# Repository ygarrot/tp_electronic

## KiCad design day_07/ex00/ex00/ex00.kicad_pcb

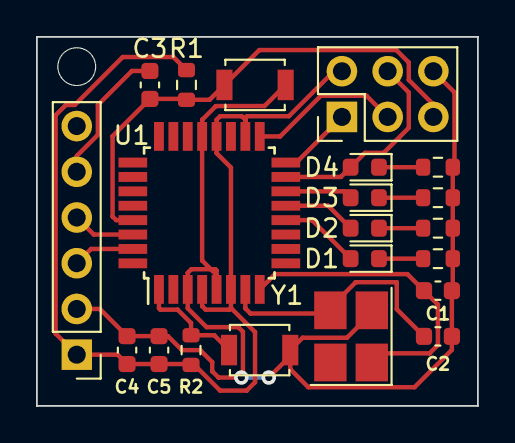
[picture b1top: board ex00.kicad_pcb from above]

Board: 2 copper layers, 24.5 x 20.5 mm, 22 parts (0 on the bottom side), 19 nets.

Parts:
C1, C2: 22pF; C_0603_1608Metric
C3, C4: 100nF; C_0603_1608Metric
C5: 10uF; C_0603_1608Metric
D1, D2, D3, D4: LED_Filled; LED_0603_1608Metric
H1: MountingHole; MountingHole_2.1mm
J1: Conn_01x06; PinHeader_1x06_P2.54mm_Vertical
J2: AVR-ISP; PinHeader_2x03_P2.54mm_Vertical
R1, R2: 10K; R_0603_1608Metric
R3, R4, R5, R6: 330R; R_0603_1608Metric
SW1, SW2: SW_Push; SW_SPST_B3U-1000P
U1: ATmega48PV-10A; TQFP-32_7x7mm_P0.8mm
Y1: 16MHz; Crystal_SMD_3225-4Pin_3.2x2.5mm_HandSoldering

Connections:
+5V: C4.1, C5.1, J1.1, J2.2 (VCC), R1.1, R2.1, U1.4 (VCC), U1.6 (VCC), U1.18 (AVCC), U1.20 (AREF)
/BUT_0: R2.2, SW2.1, U1.1 (PD3)
/LED_0: D1.2 (A), U1.12 (PB0)
/LED_1: D2.2 (A), U1.13 (PB1)
/LED_2: D3.2 (A), U1.14 (PB2)
/LED_3/MOSI: D4.2 (A), J2.4 (MOSI), U1.15 (PB3)
/MCU_RX: J1.4, U1.30 (PD0)
/MCU_TX: J1.3, U1.31 (PD1)
/MISO: J2.1 (MISO), U1.16 (PB4)
/SCK: J2.3 (SCK), U1.17 (PB5)
/XTAL1: C2.1, U1.7 (XTAL1/PB6), Y1.3
/XTAL2: C1.1, U1.8 (XTAL2/PB7), Y1.1
/~RESET: C3.2, J2.5 (~RST), R1.2, SW1.1, U1.29 (~RESET/PC6)
GND: C1.2, C2.2, C4.2, C5.2, J1.2, J2.6 (GND), R3.2, R4.2, R5.2, R6.2, SW1.2, SW2.2, U1.3 (GND), U1.5 (GND), U1.21 (GND), Y1.2
unnamed: C3.1, J1.5
unnamed: D1.1 (K), R3.1
unnamed: D2.1 (K), R4.1
unnamed: D3.1 (K), R5.1
unnamed: D4.1 (K), R6.1

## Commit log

2022-01-10 light a led
2022-01-10 delay refacto
2022-01-10 reworking on day/night
2022-01-10 still working on delayt
2022-01-11 used isr, but interrupt are not allowe
2022-01-11 its finally working wihtout loop
2022-01-11 day 00
2022-01-12 day 02
2022-01-12 ex 01 day 01
2022-01-12 clean the doc
2022-01-13 ex00 day 03
2022-01-13 ex02 day 03
2022-01-13 ex 04
2022-01-13 ex01 day 02
2022-01-13 done fixing typo in ex01
2022-01-13 ex06 day00
2022-01-14 use macro for delay because inline function doesn't work properly
2022-01-14 clear code, clear mind
2022-01-14 macro everywhere
2022-01-14 comment ex01 day 01
2022-01-14 comment day 2 3
2022-01-14 clean dupplicated code
2022-01-14 login done
2022-01-19 update day_00
2022-01-19 day 05
2022-01-20 restore day 04
2022-01-20 ex01 day 5
2022-01-20 remove unused files and folder
2022-01-20 adc done (ex00 day 06)
2022-01-21 ex02 - temperature
2022-01-21 remove opti flag
2022-01-21 ex 04 couleur analogique
2022-01-21 day06 done
2022-01-21 tech 1 ex 03 done // day done
2022-01-21 int1 instead of int0 because button change from pd3 to pd2
2022-01-21 day 04
2022-01-25 day_07
2022-01-25 day07
2022-01-25 empreintes
2022-01-26 pcb done
2022-01-27 gbr/drl
